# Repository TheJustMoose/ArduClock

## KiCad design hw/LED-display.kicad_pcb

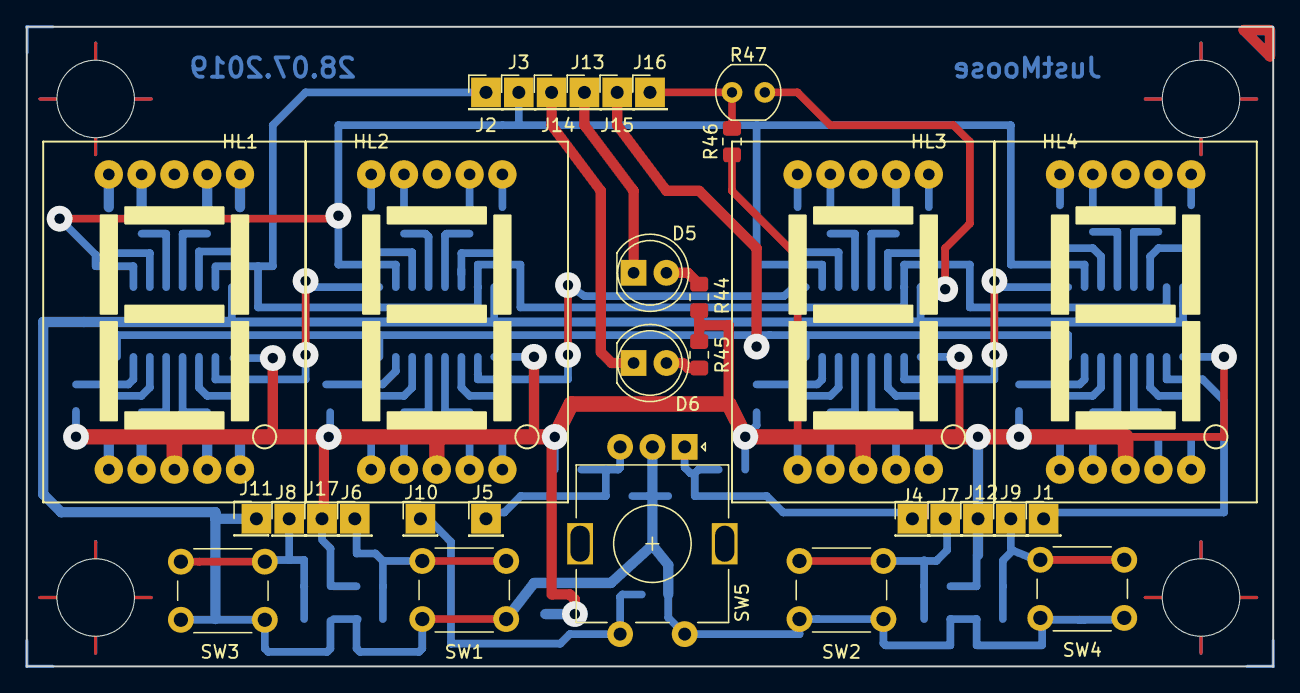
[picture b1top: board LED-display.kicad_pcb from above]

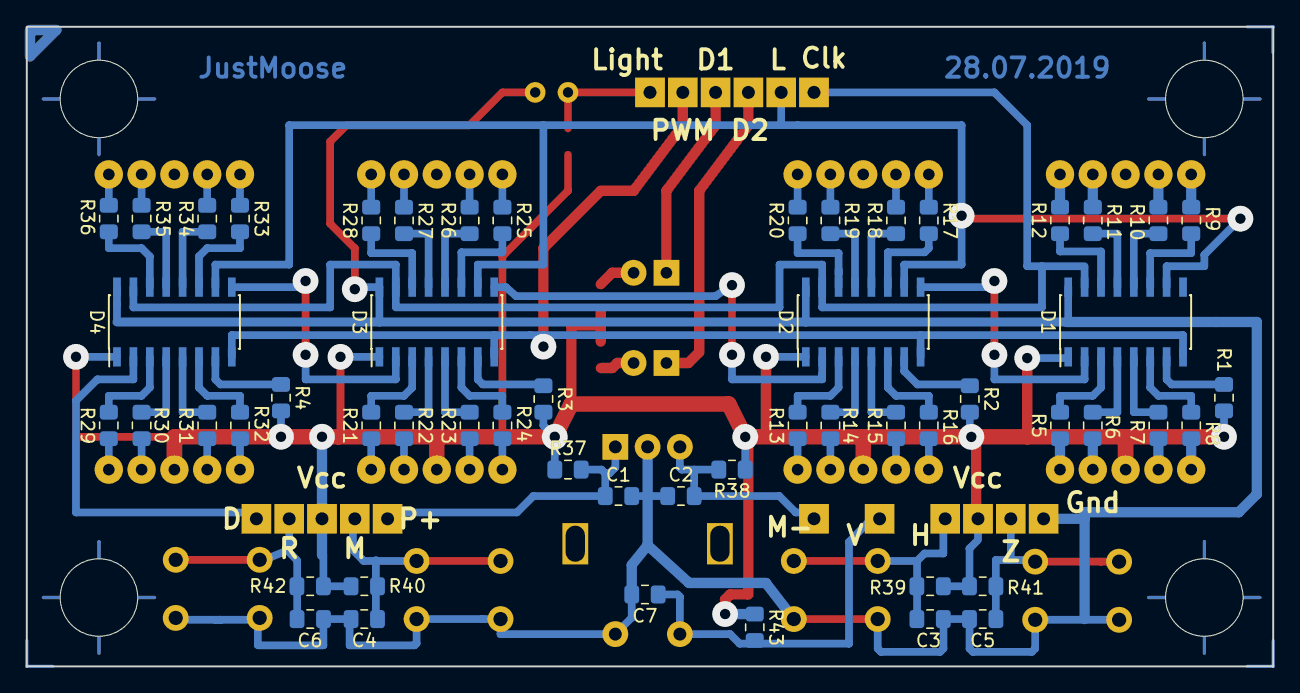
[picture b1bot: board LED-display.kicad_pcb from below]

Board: 2 copper layers, 96.5 x 49.5 mm, 90 parts (54 on the bottom side), 89 nets.

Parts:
C1, C2, C3, C4, C5, C6, C7: 4.7nF; C_0805_2012Metric_Pad1.15x1.40mm_HandSolder
D1, D2, D3, D4: TPIC6C595; SOIC-16_3.9x9.9mm_P1.27mm
D5, D6: LED; LED_D5.0mm
HL1, HL2, HL3, HL4: White7seg; 0.8 inch LED (20x28)
J1: Data; PinHeader_1x01_P2.54mm_Vertical
J2: Clock; PinHeader_1x01_P2.54mm_Vertical
J3: Latch; PinHeader_1x01_P2.54mm_Vertical
J4: Plus; PinHeader_1x01_P2.54mm_Vertical
J5: Minus; PinHeader_1x01_P2.54mm_Vertical
J6: Hour; PinHeader_1x01_P2.54mm_Vertical
J7: Minute; PinHeader_1x01_P2.54mm_Vertical
J8: Zoom; PinHeader_1x01_P2.54mm_Vertical
J9: Rsrv; PinHeader_1x01_P2.54mm_Vertical
J10: Valc; PinHeader_1x01_P2.54mm_Vertical
J11: Gnd; PinHeader_1x01_P2.54mm_Vertical
J12, J17: Vcc; PinHeader_1x01_P2.54mm_Vertical
J13: Dot1; PinHeader_1x01_P2.54mm_Vertical
J14: Dot2; PinHeader_1x01_P2.54mm_Vertical
J15: PWM; PinHeader_1x01_P2.54mm_Vertical
J16: Photo; PinHeader_1x01_P2.54mm_Vertical
MH1, MH2, MH3, MH4: MountingHole; MountingHole_6mm
R1, R2, R3, R4, R37, R38, R39, R40, R41, R42, R43: 10k; R_0805_2012Metric_Pad1.15x1.40mm_HandSolder
R5, R6, R7, R8, R9, R10, R11, R12, R13, R14, R15, R16, R17, R18, R19, R20, R21, R22, R23, R24, R25, R26, R27, R28, R29, R30, R31, R32, R33, R34, R35, R36: 2.4k; R_0805_2012Metric_Pad1.15x1.40mm_HandSolder
R44, R45, R46: R; R_0805_2012Metric_Pad1.15x1.40mm_HandSolder
R47: R_PHOTO; R_LDR_4.9x4.2mm_P2.54mm_Vertical
SW1, SW2, SW3, SW4: SW_Push; SW_PUSH_6mm_H7.3mm
SW5: Rotary_Encoder_Switch; RotaryEncoder_Alps_EC11E-Switch_Vertical_H20mm

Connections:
/Clock: D1.15, D2.15, D3.15, D4.15, J2.1
/Data: D4.2, J1.1
/Dot1: D5.1, J13.1
/Dot2: D6.1, J14.1
/Hour: C3.1, J6.1, R39.2, SW1.1
/Latch: D1.10, D2.10, D3.10, D4.10, J3.1
/Minus: C2.1, J5.1, R38.2, SW5.B
/PWM: D1.8, D2.8, D3.8, D4.8, J15.1
/Plus: C1.1, J4.1, R37.2, SW5.A
/Rsrv: C6.1, J9.1, R42.2, SW4.1
/Valc: C7.1, J10.1, R43.2, SW5.S1
/Zoom: C5.1, J8.1, R41.2, SW3.1
GND: C1.2, C2.2, C3.2, C4.2, C5.2, C6.2, C7.2, D1.16, D2.16, D3.16, D4.16, J11.1, R47.2, SW1.2, SW2.2, SW3.2, SW4.2, SW5.C, SW5.S2
unnamed: C4.1, J7.1, R40.2, SW2.1
unnamed: D1.2, D2.9
unnamed: D1.3, R5.2
unnamed: D1.4, R6.2
unnamed: D1.5, R7.2
unnamed: D1.6, R8.2
unnamed: D1.7, R1.1
unnamed: D1.11, R9.2
unnamed: D1.12, R10.2
unnamed: D1.13, R11.2
unnamed: D1.14, R12.2
unnamed: D2.2, D3.9
unnamed: D2.3, R13.2
unnamed: D2.4, R14.2
unnamed: D2.5, R15.2
unnamed: D2.6, R16.2
unnamed: D2.7, R2.1
unnamed: D2.11, R17.2
unnamed: D2.12, R18.2
unnamed: D2.13, R19.2
unnamed: D2.14, R20.2
unnamed: D3.2, D4.9
unnamed: D3.3, R21.2
unnamed: D3.4, R22.2
unnamed: D3.5, R23.2
unnamed: D3.6, R24.2
unnamed: D3.7, R3.1
unnamed: D3.11, R25.2
unnamed: D3.12, R26.2
unnamed: D3.13, R27.2
unnamed: D3.14, R28.2
unnamed: D4.3, R29.2
unnamed: D4.4, R30.2
unnamed: D4.5, R31.2
unnamed: D4.6, R32.2
unnamed: D4.7, R4.1
unnamed: D4.11, R33.2
unnamed: D4.12, R34.2
unnamed: D4.13, R35.2
unnamed: D4.14, R36.2
unnamed: D5.2, R44.2
unnamed: D6.2, R45.2
unnamed: HL1.1, R8.1
unnamed: HL1.2, R7.1
unnamed: HL1.4, R6.1
unnamed: HL1.5, R5.1
unnamed: HL1.6, R12.1
unnamed: HL1.7, R11.1
unnamed: HL1.9, R10.1
unnamed: HL1.10, R9.1
unnamed: HL2.1, R16.1
unnamed: HL2.2, R15.1
unnamed: HL2.4, R14.1
unnamed: HL2.5, R13.1
unnamed: HL2.6, R20.1
unnamed: HL2.7, R19.1
unnamed: HL2.9, R18.1
unnamed: HL2.10, R17.1
unnamed: HL3.1, R24.1
unnamed: HL3.2, R23.1
unnamed: HL3.4, R22.1
unnamed: HL3.5, R21.1
unnamed: HL3.6, R28.1
unnamed: HL3.7, R27.1
unnamed: HL3.9, R26.1
unnamed: HL3.10, R25.1
unnamed: HL4.1, R32.1
unnamed: HL4.2, R31.1
unnamed: HL4.4, R30.1
unnamed: HL4.5, R29.1
unnamed: HL4.6, R36.1
unnamed: HL4.7, R35.1
unnamed: HL4.9, R34.1
unnamed: HL4.10, R33.1
unnamed: J16.1, R46.2, R47.1
VCC: D1.1, D2.1, D3.1, D4.1, HL1.3, HL2.3, HL3.3, HL4.3, J12.1, J17.1, R1.2, R2.2, R3.2, R4.2, R37.1, R38.1, R39.1, R40.1, R41.1, R42.1, R43.1, R44.1, R45.1, R46.1

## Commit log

2019-08-23 Firmware. Initial commit.
2019-08-23 Moved from LED-display repo
2019-08-23 Faceplate in Fusion 360 format & g-code for CNC router
2019-08-23 Faceplate screenshot
2020-12-05 Some code to change LED brightness
2020-12-05 It's a static function!
